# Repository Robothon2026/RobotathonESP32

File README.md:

# Robotathon ESP32
----Alternative Movement----
There are two different movement styles. Test both and see which feels better overall. 
1. Left joystick->left motor (current)
   Right joystick->right motor
2. Left joystick->both motors (commented out)
   Right joystick-> adjusts one side depending on x position

---- Line Automation----
 If correction is negative, move left by adjusting the left wheel slower while adjusitng the right wheel faster
 if correction is positive, move right by adjusting the right wheel slower while adjusitng the left wheel faster
 if correction is zero, move straight forward at full speed
 I decided to not use the invert sensors function because it is easers to just use 1,000 for black and 0 for white
 as if i use it the other way i would have to invert everything and also i wouldn't know how that would be able to work becuase
 *right now the lineHelper function works by multiplying the sensor values by the weights but if its 1,000 in the middle and 0 on white
 then the error would go based off the middle which i dont think would be as effecient and just more complicated then using 0
 for white and 1,000 for black

----Color Automation----
How to control
1. Switch to color automation.
2. Put robot over sample color.
4. It will continue to move until it finds the color again.

----Wall Automation----
This automation part is heavily heavily heavily dependant on thresholds.
Before even attempting, you have to ensure multiple different things work together.
1. I created TIME_90_DEGREES.
   You need to debug and find how long these numbers need to be for the robot to actually rotate 90 degrees. There's no actual way to tell the robot to turn a certain degree it has to be done manually.
2. In the wallAutomation() method, there are several variables you need to test as well.
   a. wallThreshold: This is the number (cm) until the robot should treat it as a wall.
   b. rightThreshold: This is the number (cm) that tells you how far it is from the right wall.
   c. speedAdjust: This is how much the motor will slow down when it's readjusting within walls.
   1. if no wall in front, move forward.
   2. If wall in front, check right sensor, if open path, rotate 90 degrees clockwise.
   3. Else (wall on right), rotate 90 degrees counter clockwise.
           Algorithm A: While moving forward, it should stay within the right bounds. If it's 
               within these bounds, just move forward. It may still drift a bit, but that's okay.
               If it's minor, I'll leave as is. If it's major, then I'll implement PD control
               to adjust the motors based off previous value. If it is out of these bounds, then
               adjust motors based off set values (not changing).
           Algorithm B: Just move forward without worrying about centering. If rotate90CW/CCW is
               implemented well enough, then no adjustments should be necessary.
           Algorithm C: Combination of A and B. Move forward normally, but before turning 90 degrees, 
               if previous right distance > current right distance, (getting closer to wall), then
               adjust delay for TIME_90_DEGREES so that it turns for longer. If previous right
               distance < current right distance, (getting farther away from wall), then adjust
               delay for TIME_90_DEGREES so that it turns for less time.
           Notes: Calculate the connection between delay time and angle turned. Use that to adjust
               TIME_90_DEGREES based off previous and current. Calculate previous and current by
               and make them a set time apart TIME_90_DEGREES. You can then use these two to create 
               a triangle and figure out the angle it's currently moving at. From there, you can 
               calculate how much to turn to be parallel to the wall after a turn. This assumes it 
               never hits the wall which should stand true, if not there's an error in the logic. 
               The delta time is TIME_90_DEGREES because you use this to turn 90 degrees, so after 
               calculating the angle you can easily figure out how much you need to adjust to stay 
               parallel.

----Notes----
2. Adjust color offset delay so robot is over the color. 
4. I use TOP_MOTOR_SPEED for a lot of things. Don't change this variable but make another one if you think it's too fast.
5. Calculate size of wheel and radius and create equation to automatically see how long it takes to do 90 degrees.
6. Design robot so it keeps turning towards the right and then it stops when its close enough (threshold).
7. Remove left sensor integration.

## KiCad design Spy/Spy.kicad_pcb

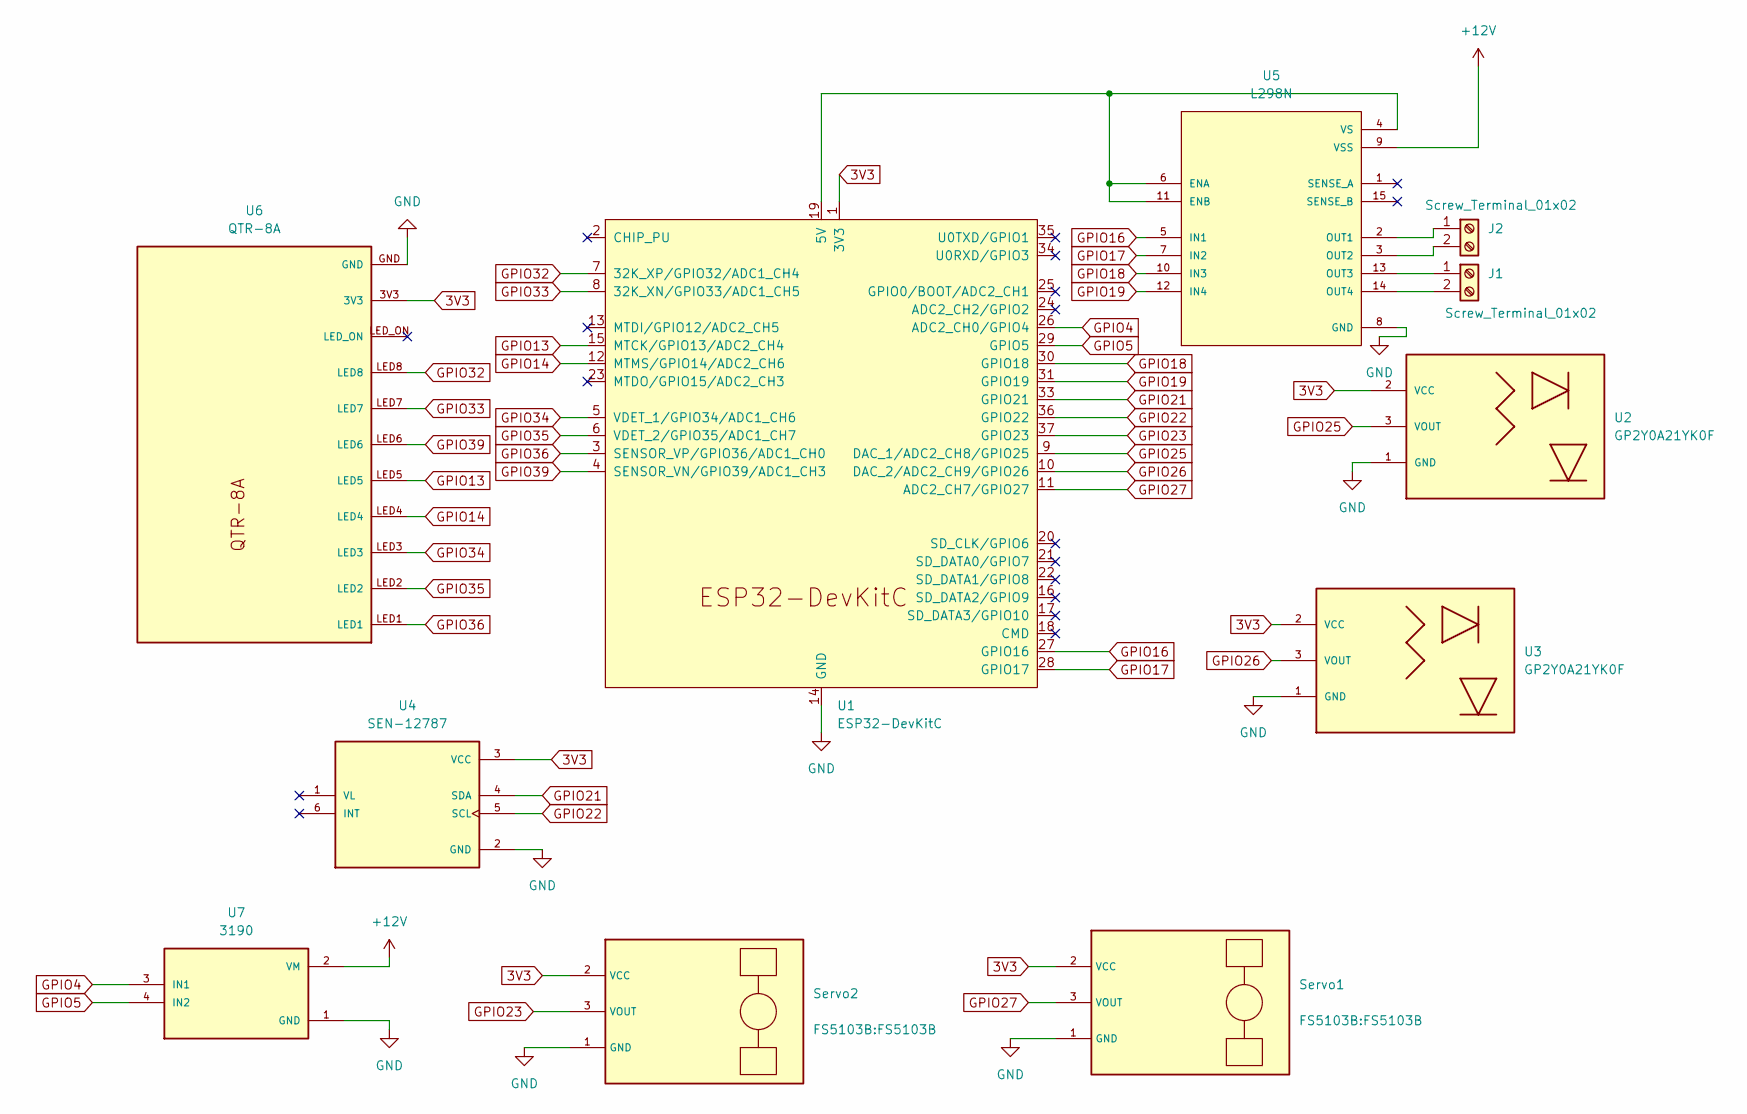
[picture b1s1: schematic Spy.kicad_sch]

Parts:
J1, J2: Screw_Terminal_01x02; PhoenixContact_MSTBA_2,5_2-G_1x02_P5.00mm_Horizontal
Servo1, Servo2: FS5103B
U1: ESP32-DevKitC
U2, U3: GP2Y0A21YK0F; 22-23-2031
U4: SEN-12787; MODULE_SEN-12787; PARTREV v10
U5: L298N; TO127P2020X500X2100-15
U6: QTR-8A
U7: 3190; MODULE_3190; PARTREV 2021-11-15

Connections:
3V3: Servo1.2 (VCC), Servo2.2 (VCC), U1.1 (3V3), U2.2 (VCC), U3.2 (VCC), U4.3 (VCC), U6.3V3
+12V: U5.9 (VSS), U7.2 (VM)
GND: Servo1.1 (GND), Servo2.1 (GND), U1.14 (GND), U1.32 (GND), U1.38 (GND), U2.1 (GND), U3.1 (GND), U4.2 (GND), U5.8 (GND), U6.GND, U7.1 (GND)
GPIO4: U1.26 (ADC2_CH0/GPIO4), U7.3 (IN1)
GPIO5: U1.29 (GPIO5), U7.4 (IN2)
GPIO13: U1.15 (MTCK/GPIO13/ADC2_CH4), U6.LED5
GPIO14: U1.12 (MTMS/GPIO14/ADC2_CH6), U6.LED4
GPIO16: U1.27 (GPIO16), U5.5 (IN1)
GPIO17: U1.28 (GPIO17), U5.7 (IN2)
GPIO18: U1.30 (GPIO18), U5.10 (IN3)
GPIO19: U1.31 (GPIO19), U5.12 (IN4)
GPIO21: U1.33 (GPIO21), U4.4 (SDA)
GPIO22: U1.36 (GPIO22), U4.5 (SCL)
GPIO23: Servo2.3 (VOUT), U1.37 (GPIO23)
GPIO25: U1.9 (DAC_1/ADC2_CH8/GPIO25), U2.3 (VOUT)
GPIO26: U1.10 (DAC_2/ADC2_CH9/GPIO26), U3.3 (VOUT)
GPIO27: Servo1.3 (VOUT), U1.11 (ADC2_CH7/GPIO27)
GPIO32: U1.7 (32K_XP/GPIO32/ADC1_CH4), U6.LED8
GPIO33: U1.8 (32K_XN/GPIO33/ADC1_CH5), U6.LED7
GPIO34: U1.5 (VDET_1/GPIO34/ADC1_CH6), U6.LED3
GPIO35: U1.6 (VDET_2/GPIO35/ADC1_CH7), U6.LED2
GPIO36: U1.3 (SENSOR_VP/GPIO36/ADC1_CH0), U6.LED1
GPIO39: U1.4 (SENSOR_VN/GPIO39/ADC1_CH3), U6.LED6
unnamed: J1.1, U5.13 (OUT3)
unnamed: J1.2, U5.14 (OUT4)
unnamed: J2.1, U5.2 (OUT1)
unnamed: J2.2, U5.3 (OUT2)
unnamed: U1.19 (5V), U5.4 (VS), U5.6 (ENA), U5.11 (ENB)

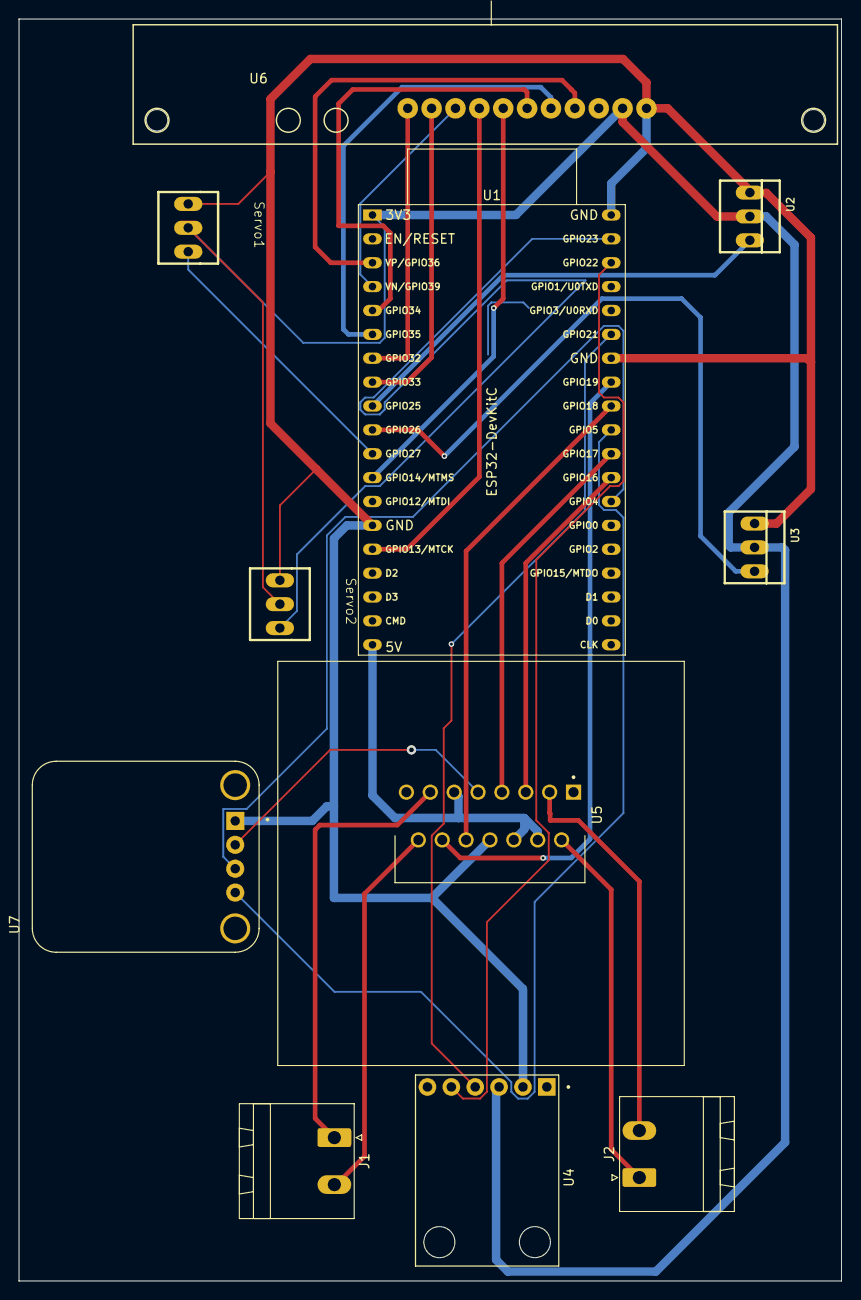
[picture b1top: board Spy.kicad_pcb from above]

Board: 2 copper layers, 87.5 x 134.2 mm, 11 parts (0 on the bottom side), 28 nets.

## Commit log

2025-09-26 Controller working
2025-09-26 checkpoint 1 and kicad
2025-09-26 complete checkpoint
2025-10-04 working controller movement
2025-10-04 fully working controller and motors
2025-10-05 cleaned up, made more efficient, added more documentation
2025-10-05 kicad libraries
2025-10-07 updated movement so left joystick -> left motor and right joystick -> right motor. Much simpler code and gives the most rotational control
2025-10-09 LineFollow Method
2025-10-09 I put a comment
2025-10-09 THis is 2nd comment
2025-10-09 schematic (1) :D
2025-10-11 pcb edited
2025-10-11 implemented automation switch, added future plans
2025-10-11 fix please
2025-10-11 added skeleton code for all sensors. All pins are placeholders.
2025-10-13 implemented all sensors, separated methods based on purpose (helper, debug, mode, setup), fixed style
2025-10-15 changed NUM_LINE_SENSORS logic and variable types
2025-10-16 new pcb
2025-10-16 first attempt at line follow automation, added.... documentation, alternative movement method to compare, movement helper to simplify coding, wifi integration to monitor wirelessly, invert sensor hel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
2025-10-16 updated README for wifi and alternative movement instructions
2025-10-18 DRV8871 driver and pin rewiring
2025-10-18 PID implemented
2025-10-19 FABIAN'S ALGORITHIM 🔥🔥
2025-10-22 rewired some stuff
2025-10-23 line test
2025-10-23 COLOR AUTOMATION DONE-- ALLEGENDLY UNTESTED
2025-10-23 added more documentation, updated README, added const values for readability
2025-10-25 read README, implemented wall automation but it needs a lot of threshold tweaking (in README), added some helper methods
2025-10-27 changed algo to work with 2 sensors
2025-10-30 Reverted and fixed version of code. Some minor PCB updates
2025-10-31 WORKING COLOR AUTOMATION YAY (maybe)
2025-11-01 updated color automation for a 'NONE' option if its not rgb. This will help avoid stopping on white, black, or any other color
2025-11-01 had error, should be able to build
2025-11-02 removed wifi and invertsensors, reformatted entire file to group methods and variables together, all sensors and motors working, color automation completed
2025-11-03 added notes.pdf
2025-11-03 Initialized in wrong location
2025-11-04 implemented three different algorithms for wall automation
2025-11-07 6 different implementations of wall automation (FR no adjust, FR adjust, FR angle adjust, LR no adjust, LR adjust, LR angle adjust)
2025-11-09 fixed alert, updated all loops to use delay so background tasks can run properly
2025-11-12 angle and collection servo implementation
2025-11-12 right pin incorrectly initialized
2025-11-13 fixed servo code
2025-11-14 semi working color and wall automation
2025-11-14 color automaiton D version
2025-11-15 transfer
2025-11-15 added blue tooth address
2025-11-15 everyone go to this
2025-11-15 bang bang
2025-11-16 comp ready code
2025-11-16 Last ever commit. Cleaned everything up and updated readme.
